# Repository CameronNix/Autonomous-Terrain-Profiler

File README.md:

## Autonomous Terrain Profiler

Servo-mounted ultrasonic obstacle-detection system on a custom 2-layer PCB. Sweeps a 180 degree arc with an HC-SR04, flags close objects with a buzzer + LEDs.

## Overview

**MCU:** ESP32-WROOM-32D (bare module, custom board — not a dev board)
**Sensor:** HC-SR04 ultrasonic, mounted on a servo for continuous bidirectional 180 degree sweep
**Alerts:** Transistor-switched (PN2222A) LEDs and passive buzzer, threshold-based proximity warnings
**PCB:** Custom 2-layer board designed from schematic to layout in KiCad

## Hardware

- **ESP32-WROOM-32D** — Bare module, GPIO-safe pin allocation (avoided strapping pins 0/2/5/12/15 and flash pins 6–11)
- **CH340C** — USB-UART bridge for programming, manual boot/reset via EN/GPIO0 buttons
- **AMS1117-3.3** — Voltage regulator, SOT-223, 10µF in/out caps
- **USB-C connector** — SHOU HAN TYPE-C 14-pin THT, 5.1kΩ CC1/CC2 pull-downs
- **HC-SR04** — Echo line level-shifted 5V→3.3V via 1kΩ/2kΩ voltage divider
- **Servo** — PWM control, GPIO12
- **PN2222A (x2)** — NPN low-side switches for buzzer (GPIO27) and LEDs (GPIO21/22)

All footprints sourced from LCSC part numbers and pulled into KiCad via the easyeda2kicad CLI tool for exact manufacturer-match footprints.

## Firmware

Written in C++ (Arduino framework). Core logic:

ESP32Servo for sweep positioning
HCSR04_ESP for ultrasonic timing/distance
Threshold-based alert logic (buzzer/LED) tied to sweep angle and distance

See firmware/terrain_profiler.ino.

## Hardware Design Files

Complete KiCad schematic and PCB layout in hardware/. The board was fully designed and verified for manufacturability (footprints checked, DRC clean) but not fabricated, the project's firmware and sweep logic were validated on a breadboard prototype instead.

## Author

Cameron Nix — Electrical and Computer Engineering, Oregon State University

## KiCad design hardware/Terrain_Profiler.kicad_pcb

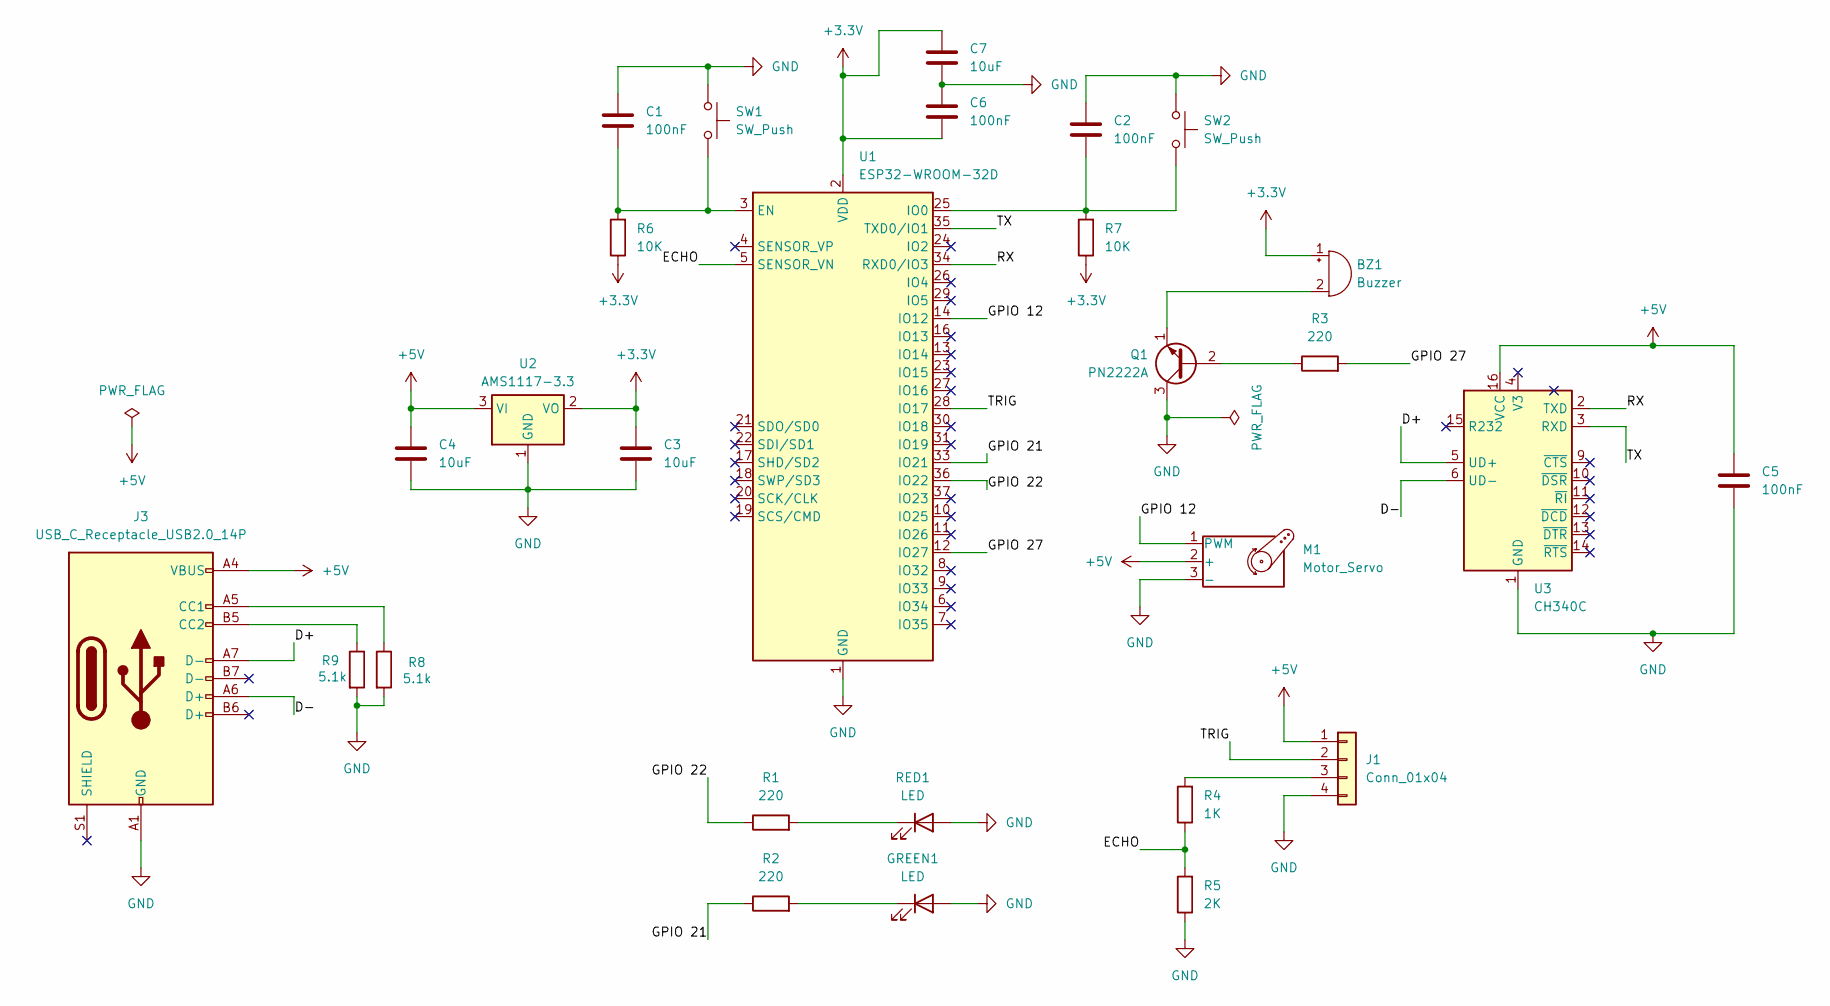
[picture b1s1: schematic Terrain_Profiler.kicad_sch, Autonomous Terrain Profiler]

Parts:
BZ1: Buzzer; BUZ-TH_BD14.1-P7.62-D1.0-FD
C1, C2, C5, C6: 100nF; CAP-TH_L13.0-W6.0-P10.00-D1.0
C3, C4, C7: 10uF; CAP-TH_L5.5-W3.8-P5.08-D0.5
GREEN1: LED; LED_D5.0mm
J1: Conn_01x04; HDR-TH_4P-P2.54-V-F
J3: USB_C_Receptacle_USB2.0_14P; USB-C-TH_SHOUHAN_TYPE-C-14PLC-H10.0
M1: Motor_Servo; HDR-TH_3P-P2.54-V-F
Q1: PN2222A; TO-92-3_L4.8-W3.7-P1.27-L
R1, R2, R3: 220; RES-TH_BD2.5-L6.5-P10.50-D0.6
R4: 1K; RES-TH_BD2.5-L6.5-P10.50-D0.6
R5: 2K; RES-TH_BD2.4-L6.3-P10.30-D0.6
R6, R7: 10K; RES-TH_BD2.5-L6.5-P10.50-D0.6
R8, R9: 5.1k; RES-TH_BD2.5-L6.5-P10.50-D0.6
RED1: LED; LED_D5.0mm
SW1, SW2: SW_Push; SW-TH_5P-L6.0-W6.0-P4.50-LS6.5
U1: ESP32-WROOM-32D; WIFIM-SMD_39P-L25.5-W18.0-P1.27-BL
U2: AMS1117-3.3; SOT-223-3_L6.5-W3.4-P2.30-LS7.0-BR
U3: CH340C; SOP-16_L10.0-W3.9-P1.27-LS6.0-BL

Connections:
+3.3V: BZ1.1 (+), C3.2, C6.1, C7.2, R6.1, R7.1, U1.2 (VDD), U2.2 (VO)
+5V: C4.2, C5.1, J1.1, J3.A4 (VBUS), J3.A9 (VBUS), J3.B4 (VBUS), J3.B9 (VBUS), M1.2 (+), U2.3 (VI), U3.16 (VCC)
/D+: J3.A7 (D-), U3.5 (UD+)
/D-: J3.A6 (D+), U3.6 (UD-)
/ECHO: R4.1, R5.2, U1.5 (SENSOR_VN)
/GPIO 12: M1.1 (PWM), U1.14 (IO12)
/GPIO 21: R2.1, U1.33 (IO21)
/GPIO 22: R1.1, U1.36 (IO22)
/GPIO 27: R3.2, U1.12 (IO27)
/RX: U1.34 (RXD0/IO3), U3.2 (TXD)
/TRIG: J1.2, U1.28 (IO17)
/TX: U1.35 (TXD0/IO1), U3.3 (RXD)
GND: C1.1, C2.1, C3.1, C4.1, C5.2, C6.2, C7.1, GREEN1.2 (A), J1.4, J3.A1 (GND), J3.A12 (GND), J3.B1 (GND), J3.B12 (GND), M1.3 (-), Q1.3 (C), R5.1, R8.2, R9.2, RED1.2 (A), SW1.1, SW2.1, U1.1 (GND), U1.15 (GND), U1.38 (GND), U1.39 (GND), U2.1 (GND), U3.1 (GND)
unnamed: BZ1.2 (-), Q1.1 (E)
unnamed: GREEN1.1 (K), R2.2
unnamed: J1.3, R4.2
unnamed: J3.A5 (CC1), R8.1
unnamed: J3.B5 (CC2), R9.1
unnamed: Q1.2 (B), R3.1
unnamed: R1.2, RED1.1 (K)
unnamed: C1.2, R6.2, SW1.2, U1.3 (EN)
unnamed: C2.2, R7.2, SW2.2, U1.25 (IO0)

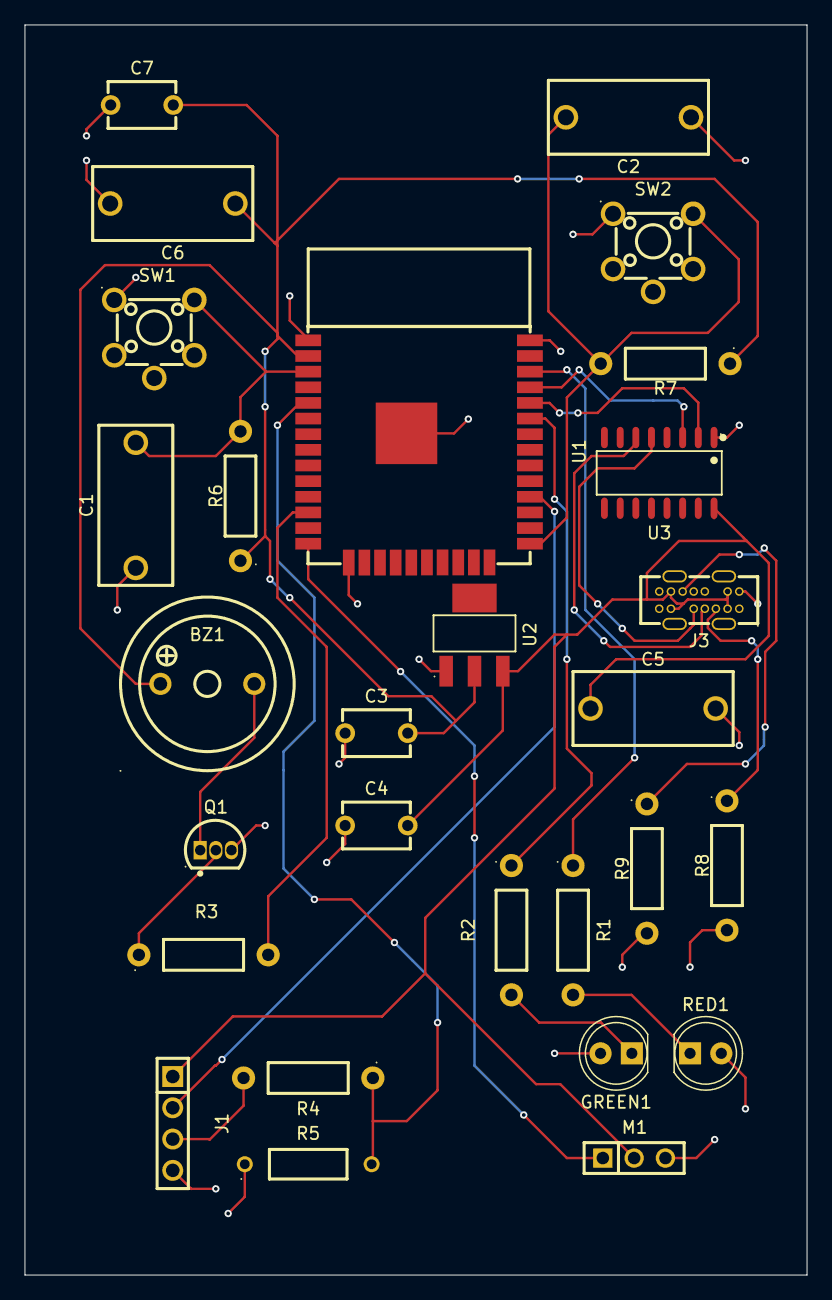
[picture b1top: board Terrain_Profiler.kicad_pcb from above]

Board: 2 copper layers, 63.5 x 101.5 mm, 28 parts (0 on the bottom side), 22 nets.
